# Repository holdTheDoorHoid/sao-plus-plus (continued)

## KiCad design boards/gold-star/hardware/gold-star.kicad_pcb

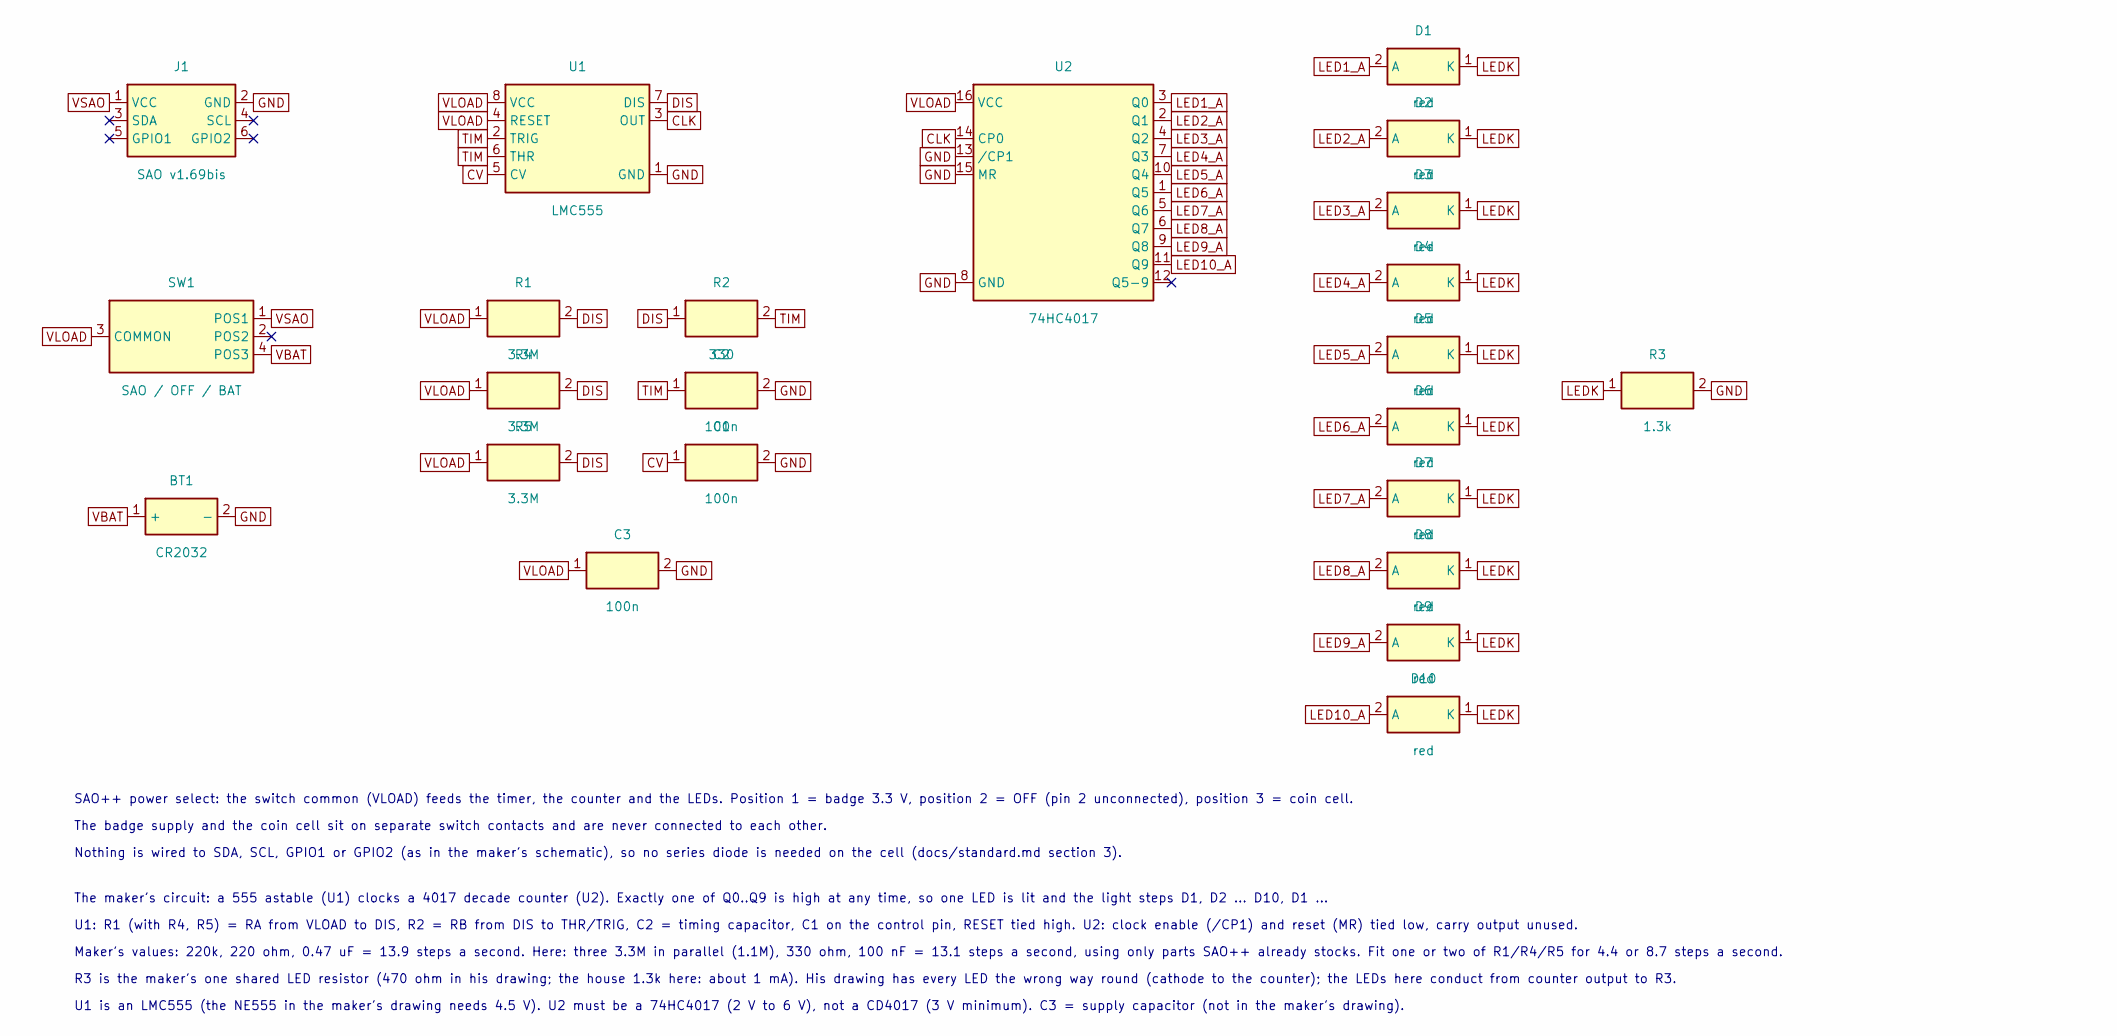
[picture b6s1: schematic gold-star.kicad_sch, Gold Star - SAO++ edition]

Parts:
BT1: CR2032; SAOPP_BAT-01_CR2032_SMD_TE_BAT-HLD-001; MPN BAT-HLD-001; LCSC C7501066
C1, C2, C3: 100n; SAOPP_C_0603_1608Metric; MPN CC0603KRX7R9BB104; LCSC C14663
D1, D2, D3, D4, D5, D6, D7, D8, D9, D10: red; SAOPP_LED-10_1206_ReverseMount_ThroughBoard; MPN LTST-C230KRKT; LCSC C125107
J1: SAO v1.69bis; SAOPP_CONN-01_BoxHeader_2x03_P2.54mm_SMD_XFCN_BH254VS-6P; MPN BH254VS-6P; LCSC C492445
R1, R4, R5: 3.3M; R_0603_1608Metric; MPN 0603WAF3304T5E; LCSC C26096
R2: 330; SAOPP_R_0603_1608Metric; MPN 0603WAF3300T5E; LCSC C23138
R3: 1.3k; SAOPP_R_0603_1608Metric; MPN 0603WAF1301T5E; LCSC C22767
SW1: SAO / OFF / BAT; SAOPP_SW-01_Slide_SP3T_CK_PCM13SMTR; MPN PCM13SMTR; LCSC C221842
U1: LMC555; SOIC-8_3.9x4.9mm_P1.27mm; MPN LMC555CMX/NOPB; LCSC C90760
U2: 74HC4017; SOIC-16_3.9x9.9mm_P1.27mm; MPN 74HC4017 (SOIC-16)

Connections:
CLK: U1.3 (OUT), U2.14 (CP0)
CV: C1.1, U1.5 (CV)
DIS: R1.2, R2.1, R4.2, R5.2, U1.7 (DIS)
GND: BT1.2 (-), C1.2, C2.2, C3.2, J1.2 (GND), R3.2, U1.1 (GND), U2.8 (GND), U2.13 (/CP1), U2.15 (MR)
LED1_A: D1.2 (A), U2.3 (Q0)
LED2_A: D2.2 (A), U2.2 (Q1)
LED3_A: D3.2 (A), U2.4 (Q2)
LED4_A: D4.2 (A), U2.7 (Q3)
LED5_A: D5.2 (A), U2.10 (Q4)
LED6_A: D6.2 (A), U2.1 (Q5)
LED7_A: D7.2 (A), U2.5 (Q6)
LED8_A: D8.2 (A), U2.6 (Q7)
LED9_A: D9.2 (A), U2.9 (Q8)
LED10_A: D10.2 (A), U2.11 (Q9)
LEDK: D1.1 (K), D2.1 (K), D3.1 (K), D4.1 (K), D5.1 (K), D6.1 (K), D7.1 (K), D8.1 (K), D9.1 (K), D10.1 (K), R3.1
TIM: C2.1, R2.2, U1.2 (TRIG), U1.6 (THR)
VBAT: BT1.1 (+), SW1.4 (POS3)
VLOAD: C3.1, R1.1, R4.1, R5.1, SW1.3 (COMMON), U1.4 (RESET), U1.8 (VCC), U2.16 (VCC)
VSAO: J1.1 (VCC), SW1.1 (POS1)

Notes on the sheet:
SAO++ power select: the switch common (VLOAD) feeds the timer, the counter and the LEDs. Position 1 = badge 3.3 V, position 2 = OFF (pin 2 unconnected), position 3 = coin cell.
The badge supply and the coin cell sit on separate switch contacts and are never connected to each other.
Nothing is wired to SDA, SCL, GPIO1 or GPIO2 (as in the maker's schematic), so no series diode is needed on the cell (docs/standard.md section 3).
The maker's circuit: a 555 astable (U1) clocks a 4017 decade counter (U2). Exactly one of Q0..Q9 is high at any time, so one LED is lit and the light steps D1, D2 ... D10, D1 ...
U1: R1 (with R4, R5) = RA from VLOAD to DIS, R2 = RB from DIS to THR/TRIG, C2 = timing capacitor, C1 on the control pin, RESET tied high. U2: clock enable (/CP1) and reset (MR) tied low, carry output unused.
Maker's values: 220k, 220 ohm, 0.47 uF = 13.9 steps a second. Here: three 3.3M in parallel (1.1M), 330 ohm, 100 nF = 13.1 steps a second, using only parts SAO++ already stocks. Fit one or two of R1/R4/R5 for 4.4 or 8.7 steps a second.
R3 is the maker's one shared LED resistor (470 ohm in his drawing; the house 1.3k here: about 1 mA). His drawing has every LED the wrong way round (cathode to the counter); the LEDs here conduct from counter output to R3.
U1 is an LMC555 (the NE555 in the maker's drawing needs 4.5 V). U2 must be a 74HC4017 (2 V to 6 V), not a CD4017 (3 V minimum). C3 = supply capacitor (not in the maker's drawing).

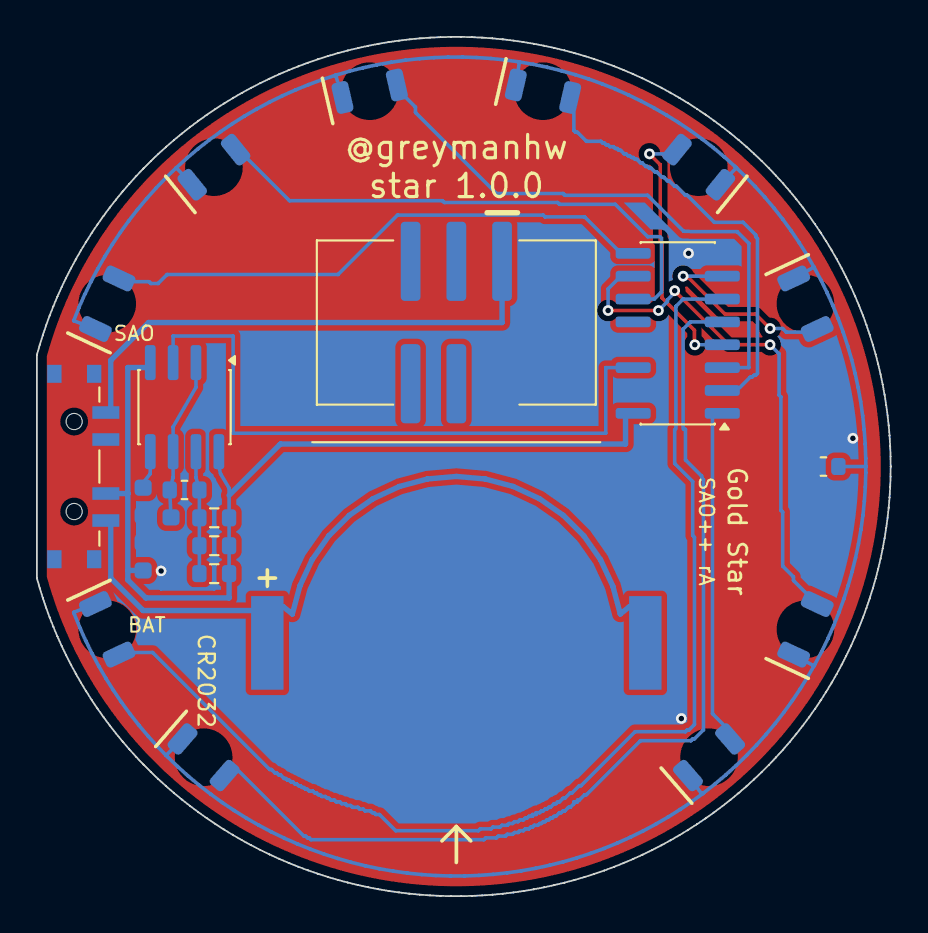
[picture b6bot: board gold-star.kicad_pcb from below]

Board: 2 copper layers, 47.4 x 47.7 mm, 23 parts (23 on the bottom side), 19 nets.

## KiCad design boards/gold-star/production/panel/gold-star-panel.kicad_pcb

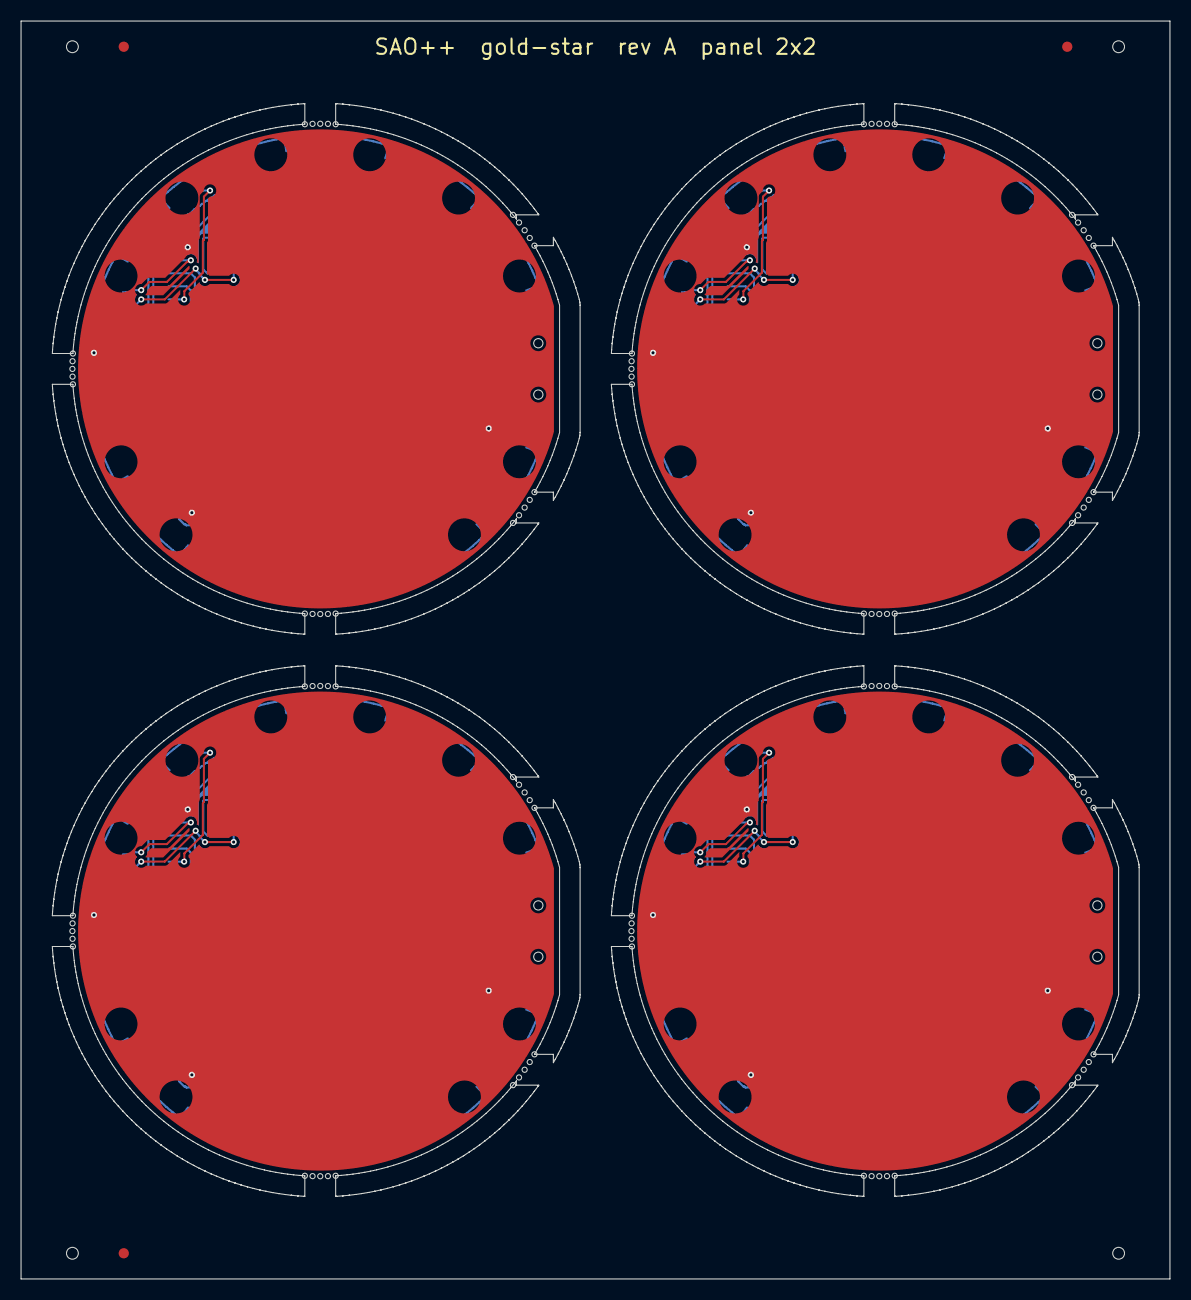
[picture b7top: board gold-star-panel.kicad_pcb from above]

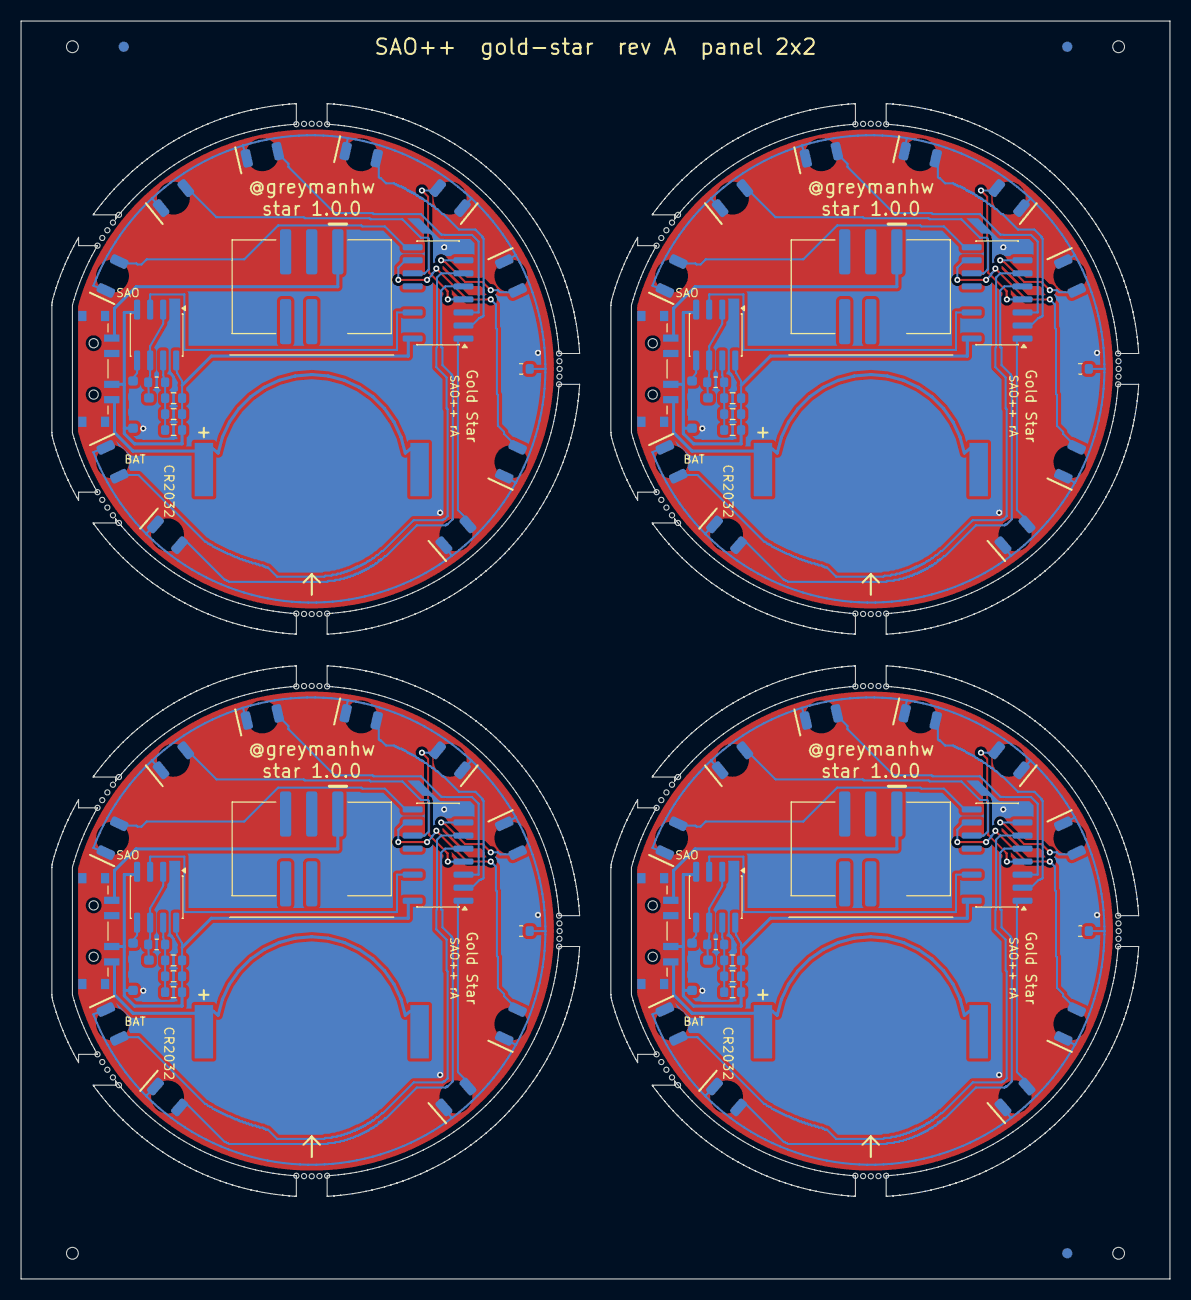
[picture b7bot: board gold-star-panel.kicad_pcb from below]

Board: 2 copper layers, 111.9 x 122.5 mm, 92 parts (92 on the bottom side), 76 nets.

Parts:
BT101, BT201, BT301, BT401: CR2032; SAOPP_BAT-01_CR2032_SMD_TE_BAT-HLD-001
C101, C102, C103, C201, C202, C203, C301, C302, C303, C401, C402, C403: 100n; SAOPP_C_0603_1608Metric
D101, D102, D103, D104, D105, D106, D107, D108, D109, D110, D201, D202, D203, D204, D205, D206, D207, D208, D209, D210, D301, D302, D303, D304, D305, D306, D307, D308, D309, D310, D401, D402, D403, D404, D405, D406, D407, D408, D409, D410: red; SAOPP_LED-10_1206_ReverseMount_ThroughBoard
J101, J201, J301, J401: SAO v1.69bis; SAOPP_CONN-01_BoxHeader_2x03_P2.54mm_SMD_XFCN_BH254VS-6P
R101, R104, R105, R201, R204, R205, R301, R304, R305, R401, R404, R405: 3.3M; R_0603_1608Metric
R102, R202, R302, R402: 330; SAOPP_R_0603_1608Metric
R103, R203, R303, R403: 1.3k; SAOPP_R_0603_1608Metric
SW101, SW201, SW301, SW401: SAO / OFF / BAT; SAOPP_SW-01_Slide_SP3T_CK_PCM13SMTR
U101, U201, U301, U401: LMC555; SOIC-8_3.9x4.9mm_P1.27mm
U102, U202, U302, U402: 74HC4017; SOIC-16_3.9x9.9mm_P1.27mm

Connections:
B2-CLK: U201.3, U202.14
B2-CV: C201.1, U201.5
B2-DIS: R201.2, R202.1, R204.2, R205.2, U201.7
B2-GND: BT201.2, C201.2, C202.2, C203.2, J201.2, R203.2, U201.1, U202.8, U202.13, U202.15
B2-LED1_A: D201.2, U202.3
B2-LED2_A: D202.2, U202.2
B2-LED3_A: D203.2, U202.4
B2-LED4_A: D204.2, U202.7
B2-LED5_A: D205.2, U202.10
B2-LED6_A: D206.2, U202.1
B2-LED7_A: D207.2, U202.5
B2-LED8_A: D208.2, U202.6
B2-LED9_A: D209.2, U202.9
B2-LED10_A: D210.2, U202.11
B2-LEDK: D201.1, D202.1, D203.1, D204.1, D205.1, D206.1, D207.1, D208.1, D209.1, D210.1, R203.1
B2-TIM: C202.1, R202.2, U201.2, U201.6
B2-VBAT: BT201.1, SW201.4
B2-VLOAD: C203.1, R201.1, R204.1, R205.1, SW201.3, U201.4, U201.8, U202.16
B2-VSAO: J201.1, SW201.1
B3-CLK: U301.3, U302.14
B3-CV: C301.1, U301.5
B3-DIS: R301.2, R302.1, R304.2, R305.2, U301.7
B3-GND: BT301.2, C301.2, C302.2, C303.2, J301.2, R303.2, U301.1, U302.8, U302.13, U302.15
B3-LED1_A: D301.2, U302.3
B3-LED2_A: D302.2, U302.2
B3-LED3_A: D303.2, U302.4
B3-LED4_A: D304.2, U302.7
B3-LED5_A: D305.2, U302.10
B3-LED6_A: D306.2, U302.1
B3-LED7_A: D307.2, U302.5
B3-LED8_A: D308.2, U302.6
B3-LED9_A: D309.2, U302.9
B3-LED10_A: D310.2, U302.11
B3-LEDK: D301.1, D302.1, D303.1, D304.1, D305.1, D306.1, D307.1, D308.1, D309.1, D310.1, R303.1
B3-TIM: C302.1, R302.2, U301.2, U301.6
B3-VBAT: BT301.1, SW301.4
B3-VLOAD: C303.1, R301.1, R304.1, R305.1, SW301.3, U301.4, U301.8, U302.16
B3-VSAO: J301.1, SW301.1
B4-CLK: U401.3, U402.14
B4-CV: C401.1, U401.5
B4-DIS: R401.2, R402.1, R404.2, R405.2, U401.7
B4-GND: BT401.2, C401.2, C402.2, C403.2, J401.2, R403.2, U401.1, U402.8, U402.13, U402.15
B4-LED1_A: D401.2, U402.3
B4-LED2_A: D402.2, U402.2
B4-LED3_A: D403.2, U402.4
B4-LED4_A: D404.2, U402.7
B4-LED5_A: D405.2, U402.10
B4-LED6_A: D406.2, U402.1
B4-LED7_A: D407.2, U402.5
B4-LED8_A: D408.2, U402.6
B4-LED9_A: D409.2, U402.9
B4-LED10_A: D410.2, U402.11
B4-LEDK: D401.1, D402.1, D403.1, D404.1, D405.1, D406.1, D407.1, D408.1, D409.1, D410.1, R403.1
B4-TIM: C402.1, R402.2, U401.2, U401.6
B4-VBAT: BT401.1, SW401.4
B4-VLOAD: C403.1, R401.1, R404.1, R405.1, SW401.3, U401.4, U401.8, U402.16
B4-VSAO: J401.1, SW401.1
CLK: U101.3, U102.14
CV: C101.1, U101.5
DIS: R101.2, R102.1, R104.2, R105.2, U101.7
GND: BT101.2, C101.2, C102.2, C103.2, J101.2, R103.2, U101.1, U102.8, U102.13, U102.15
LED1_A: D101.2, U102.3
LED2_A: D102.2, U102.2
LED3_A: D103.2, U102.4
LED4_A: D104.2, U102.7
LED5_A: D105.2, U102.10
LED6_A: D106.2, U102.1
LED7_A: D107.2, U102.5
LED8_A: D108.2, U102.6
LED9_A: D109.2, U102.9
LED10_A: D110.2, U102.11
LEDK: D101.1, D102.1, D103.1, D104.1, D105.1, D106.1, D107.1, D108.1, D109.1, D110.1, R103.1
TIM: C102.1, R102.2, U101.2, U101.6
VBAT: BT101.1, SW101.4
VLOAD: C103.1, R101.1, R104.1, R105.1, SW101.3, U101.4, U101.8, U102.16
VSAO: J101.1, SW101.1

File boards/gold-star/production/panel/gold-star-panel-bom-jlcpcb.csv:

Comment,Designator,Footprint,LCSC Part #
CR2032,"BT101,BT201,BT301,BT401",SAOPP_BAT-01_CR2032_SMD_TE_BAT-HLD-001,C7501066
100n,"C101,C102,C103,C201,C202,C203,C301,C302,C303,C401,C402,C403",SAOPP_C_0603_1608Metric,C14663
red,"D101,D102,D103,D104,D105,D106,D107,D108,D109,D110,D201,D202,D203,D204,D205,D206,D207,D208,D209,D210,D301,D302,D303,D304,D305,D306,D307,D308,D309,D310,D401,D402,D403,D404,D405,D406,D407,D408,D409,D410",SAOPP_LED-10_1206_ReverseMount_ThroughBoard,C125107
SAO v1.69bis,"J101,J201,J301,J401",SAOPP_CONN-01_BoxHeader_2x03_P2.54mm_SMD_XFCN_BH254VS-6P,C492445
3.3M,"R101,R104,R105,R201,R204,R205,R301,R304,R305,R401,R404,R405",R_0603_1608Metric,C26096
330,"R102,R202,R302,R402",SAOPP_R_0603_1608Metric,C23138
1.3k,"R103,R203,R303,R403",SAOPP_R_0603_1608Metric,C22767
SAO / OFF / BAT,"SW101,SW201,SW301,SW401",SAOPP_SW-01_Slide_SP3T_CK_PCM13SMTR,C221842
LMC555,"U101,U201,U301,U401",SOIC-8_3.9x4.9mm_P1.27mm,C90760
74HC4017,"U102,U202,U302,U402",SOIC-16_3.9x9.9mm_P1.27mm,

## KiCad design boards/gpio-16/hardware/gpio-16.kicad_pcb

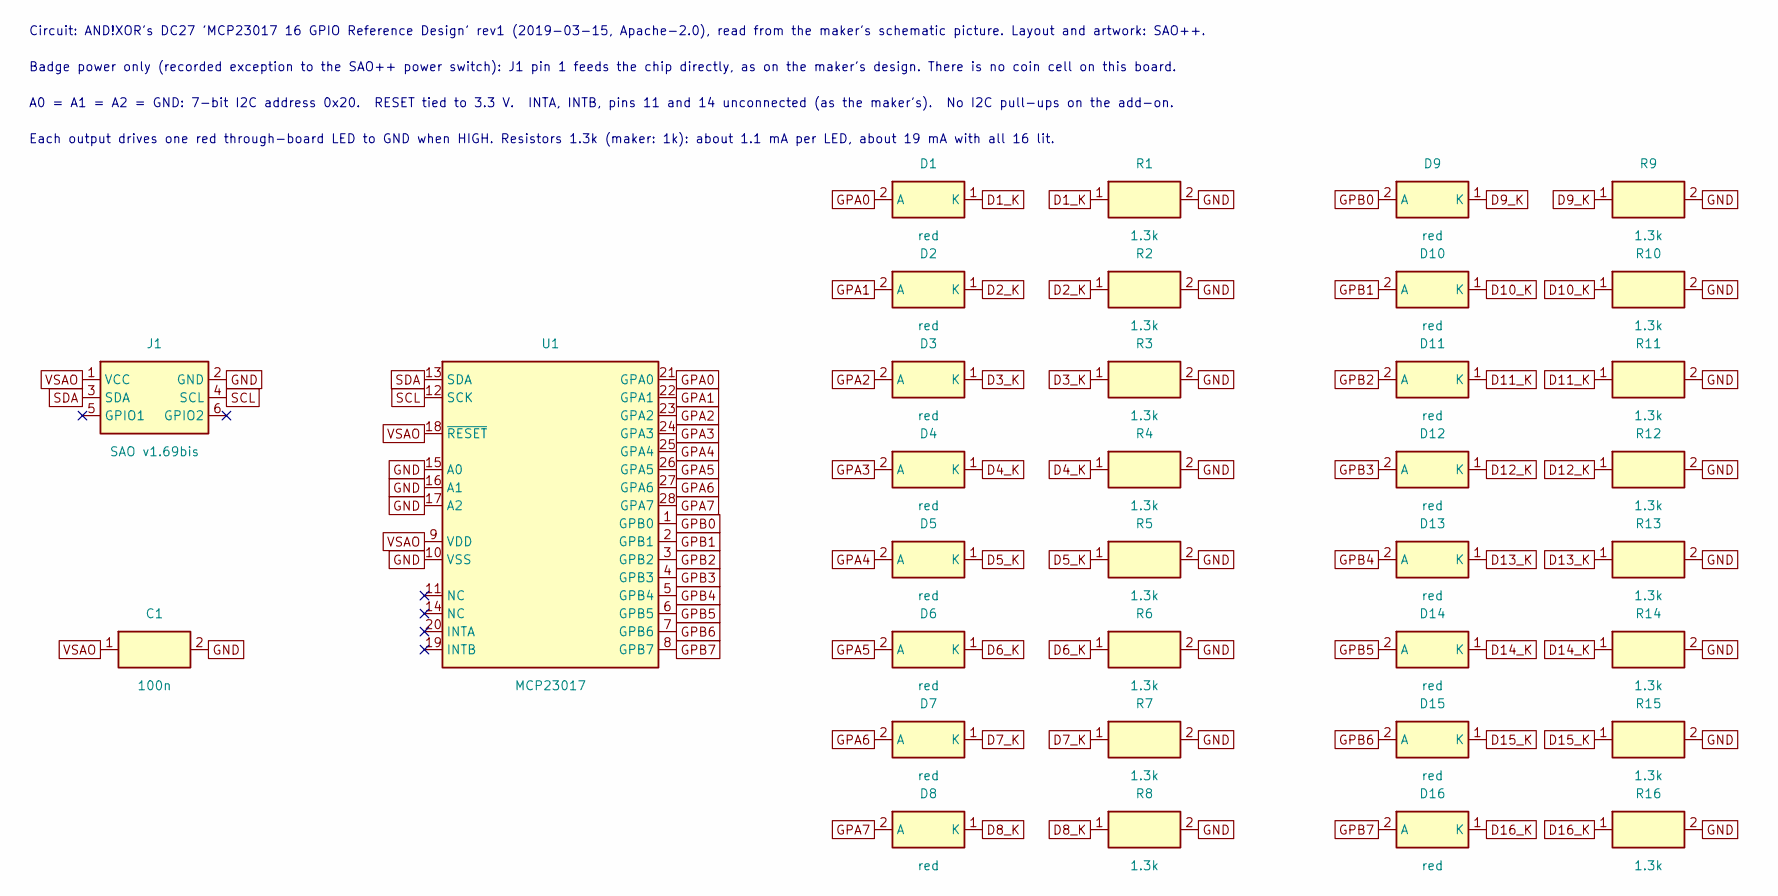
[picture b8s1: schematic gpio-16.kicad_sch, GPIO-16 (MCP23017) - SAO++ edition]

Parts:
C1: 100n; SAOPP_C_0603_1608Metric; MPN CC0603KRX7R9BB104; LCSC C14663
D1, D2, D3, D4, D5, D6, D7, D8, D9, D10, D11, D12, D13, D14, D15, D16: red; SAOPP_LED-10_1206_ReverseMount_ThroughBoard; MPN LTST-C230KRKT; LCSC C125107
J1: SAO v1.69bis; SAOPP_CONN-01_BoxHeader_2x03_P2.54mm_SMD_XFCN_BH254VS-6P; MPN BH254VS-6P; LCSC C492445
R1, R2, R3, R4, R5, R6, R7, R8, R9, R10, R11, R12, R13, R14, R15, R16: 1.3k; SAOPP_R_0603_1608Metric; MPN 0603WAF1301T5E; LCSC C22767
U1: MCP23017; SSOP-28_5.3x10.2mm_P0.65mm_Microchip_C04-2073A; MPN MCP23017T-E/SS; LCSC C558584

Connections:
D1_K: D1.1 (K), R1.1
D2_K: D2.1 (K), R2.1
D3_K: D3.1 (K), R3.1
D4_K: D4.1 (K), R4.1
D5_K: D5.1 (K), R5.1
D6_K: D6.1 (K), R6.1
D7_K: D7.1 (K), R7.1
D8_K: D8.1 (K), R8.1
D9_K: D9.1 (K), R9.1
D10_K: D10.1 (K), R10.1
D11_K: D11.1 (K), R11.1
D12_K: D12.1 (K), R12.1
D13_K: D13.1 (K), R13.1
D14_K: D14.1 (K), R14.1
D15_K: D15.1 (K), R15.1
D16_K: D16.1 (K), R16.1
GND: C1.2, J1.2 (GND), R1.2, R2.2, R3.2, R4.2, R5.2, R6.2, R7.2, R8.2, R9.2, R10.2, R11.2, R12.2, R13.2, R14.2, R15.2, R16.2, U1.10 (VSS), U1.15 (A0), U1.16 (A1), U1.17 (A2)
GPA0: D1.2 (A), U1.21 (GPA0)
GPA1: D2.2 (A), U1.22 (GPA1)
GPA2: D3.2 (A), U1.23 (GPA2)
GPA3: D4.2 (A), U1.24 (GPA3)
GPA4: D5.2 (A), U1.25 (GPA4)
GPA5: D6.2 (A), U1.26 (GPA5)
GPA6: D7.2 (A), U1.27 (GPA6)
GPA7: D8.2 (A), U1.28 (GPA7)
GPB0: D9.2 (A), U1.1 (GPB0)
GPB1: D10.2 (A), U1.2 (GPB1)
GPB2: D11.2 (A), U1.3 (GPB2)
GPB3: D12.2 (A), U1.4 (GPB3)
GPB4: D13.2 (A), U1.5 (GPB4)
GPB5: D14.2 (A), U1.6 (GPB5)
GPB6: D15.2 (A), U1.7 (GPB6)
GPB7: D16.2 (A), U1.8 (GPB7)
SCL: J1.4 (SCL), U1.12 (SCK)
SDA: J1.3 (SDA), U1.13 (SDA)
VSAO: C1.1, J1.1 (VCC), U1.9 (VDD), U1.18 (~RESET)

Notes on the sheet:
Circuit: AND!XOR's DC27 'MCP23017 16 GPIO Reference Design' rev1 (2019-03-15, Apache-2.0), read from the maker's schematic picture. Layout and artwork: SAO++.
Badge power only (recorded exception to the SAO++ power switch): J1 pin 1 feeds the chip directly, as on the maker's design. There is no coin cell on this board.
A0 = A1 = A2 = GND: 7-bit I2C address 0x20. RESET tied to 3.3 V. INTA, INTB, pins 11 and 14 unconnected (as the maker's). No I2C pull-ups on the add-on.
Each output drives one red through-board LED to GND when HIGH. Resistors 1.3k (maker: 1k): about 1.1 mA per LED, about 19 mA with all 16 lit.

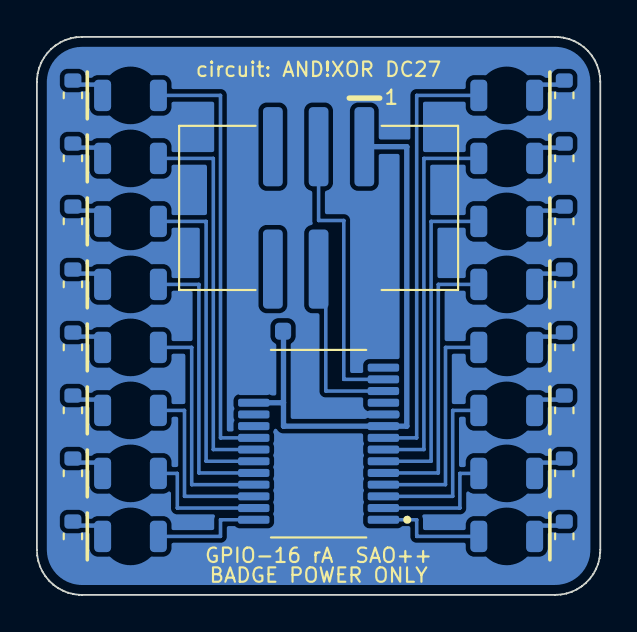
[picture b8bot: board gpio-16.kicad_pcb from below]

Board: 2 copper layers, 31.3 x 31.0 mm, 35 parts (35 on the bottom side), 36 nets.

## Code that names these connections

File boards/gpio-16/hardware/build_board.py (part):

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Layout (front view, x grows right, y grows down, board centred on 0, 0):
  - 31.3 x 31.0 mm rounded rectangle
  - two columns of eight through-board LEDs: port B down the left edge (B7 at the top), port A down the right edge
    (A0 at the top), so the sixteen lights run clockwise from bottom left in pin order GPB0..GPB7, GPA0..GPA7
  - SAO connector in the upper middle (key up), the MCP23017 below it with its power / I2C end toward the connector
  - each LED's resistor stands outside it, with its ground end in a ground ring that runs round the board edge
  - every track is on the back copper; there are no vias and no holes. The front carries no copper at all.
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SLOT = [5.45, 5.85, 6.25, 6.65, 7.05, 7.45, 7.85]      # |x| of the seven upward LED tracks beside the chip
VDD_X = 4.9                         # |x| of the supply track, innermost on the left

# LED of each chip pin. Left column top to bottom = pins 8..1 (GPB7..GPB0); right column top to bottom = pins 21..28
# (GPA0..GPA7). D1..D8 = GPA0..GPA7, D9..D16 = GPB0..GPB7 (circuit.json).
LEFT = [(f"D{9 + b}", b) for b in range(7, -1, -1)]      # (ref, bit) for rows 0..7
RIGHT = [(f"D{1 + b}", b) for b in range(8)]
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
